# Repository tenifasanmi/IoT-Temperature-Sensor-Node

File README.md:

# IoT Temperature Sensor Node
## Overview
This project demonstrates fog and cloud computing for IoT sensor data, differing in terms of latency and response time.
A DHT11 sensor connected to an ESP32 collects temperature and humidity data, and sends it to a Raspberry Pi acting as a fog node (local processing) or to a cloud server (Adafruit IO) for remote processing. For this project, I made use of Freenove's ESP32 WROOM Development Board. This choice was mainly due to its small size and wifi/Bluetooth capabilities. I couldn't find a footprint/symbol for this board online for use in my schematics, so I designed the PCB using a pin header connector to connect my board to the PCB. The pin headers correspond with the pins of the devboard and allow for connection between the board and the temperature sensor. The DHT11 can also be interchanged with the DHT22 temperature sensor, which offers higher accuracy and a wider temperature range, but is more costly.
Initially, this system was tested using a Raspberry Pi 4B as the sensor node and my local PC as the fog node for processing. Due to constraints in real-world applications, such as size, as well as the fact that this is a small-scale device which doesn't require all the functionalities of a Raspberry Pi 4B, this project was switched to an ESP32. For this project, the code was written in Python using the Raspberry Pi; however, I have decided to implement it in C for the ESP32. The functionality remains the same for both implementations.

## Raspberry Pi-based IoT Sensor Node
### Workflow
* The Raspberry Pi reads data from the DHT11 sensor.
* It publishes the readings to the PC (Fog Node) via MQTT.
* The Fog Node locally processes the data, sends a feedback message (e.g., “Too cold, turn on heater”), and forwards the data to the cloud.
* The Cloud (Adafruit IO) stores the readings, allows remote access, and sends cloud-level feedback back to the system.

### Materials Used
* Raspberry Pi 4B
* DHT11 Sensor
* Fog Node (Windows PC)
* Cloud Server (Adafruit IO)
* MQTT Broker

#### Wiring Diagram
<p align=center>

#### Schematic
<p align=center>

## ESP 32-based IoT Sensor Node
### Workflow
* The ESP32 reads data from the DHT11 sensor.
* It publishes the readings to the Raspberry Pi (Fog Node) via MQTT.
* The Fog Node locally processes the data, sends a feedback message (e.g., “Too cold, turn on heater”), and forwards the data back to the ESP32.
* For the Cloud implementation using Adafruit IO, the data is sent to the cloud server, where data processing takes place feedback.

### Materials Used
* ESP32-WROOM-32E Dev Board
* DHT11 Sensor
* Fog Node (Raspberry Pi)
* Custom PCB for connecting DHT11 to ESP32-WROOM-32E Dev Board
* MQTT Broker

#### Custom PCB Connection Board
<p align=center /p>

#### Schematic
<p align = center /p>

## Results
Fog processing provides quicker response times since computations occur closer to the sensor, while cloud processing offers better scalability and data visibility at the cost of higher latency.

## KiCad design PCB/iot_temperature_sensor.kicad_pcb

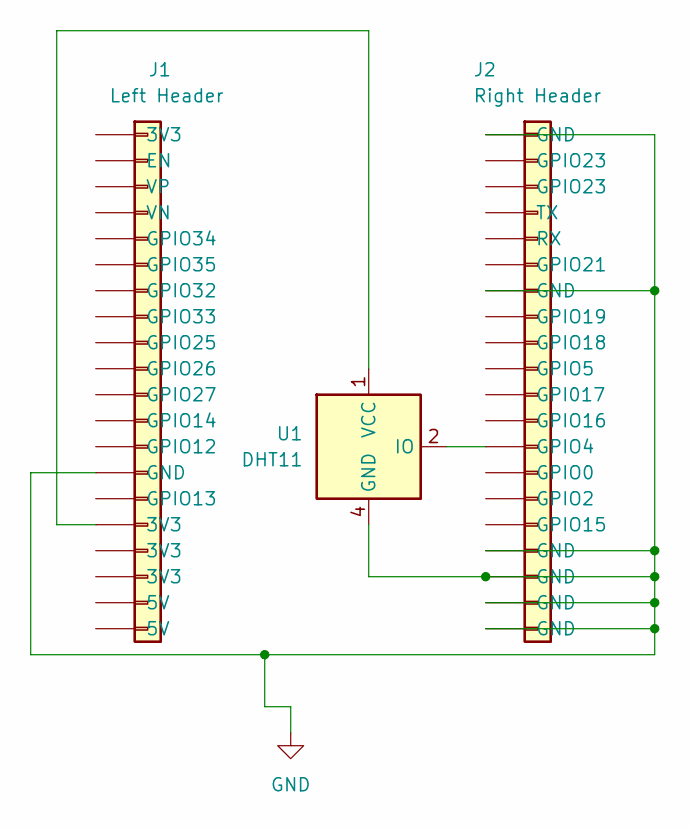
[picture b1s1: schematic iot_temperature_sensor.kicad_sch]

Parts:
J1: Left Header; PinHeader_1x20_P2.54mm_Vertical
J2: Right Header; PinHeader_1x20_P2.54mm_Vertical
U1: DHT11; Aosong_DHT11_5.5x12.0_P2.54mm

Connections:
GND: J1.14 (GND), J2.1 (GND), J2.7 (GND), J2.17 (GND), J2.18 (GND), J2.19 (GND), J2.20 (GND), U1.4 (GND)
unnamed: J2.13 (GPIO4), U1.2 (IO)
unnamed: J1.16 (3V3), U1.1 (VCC)

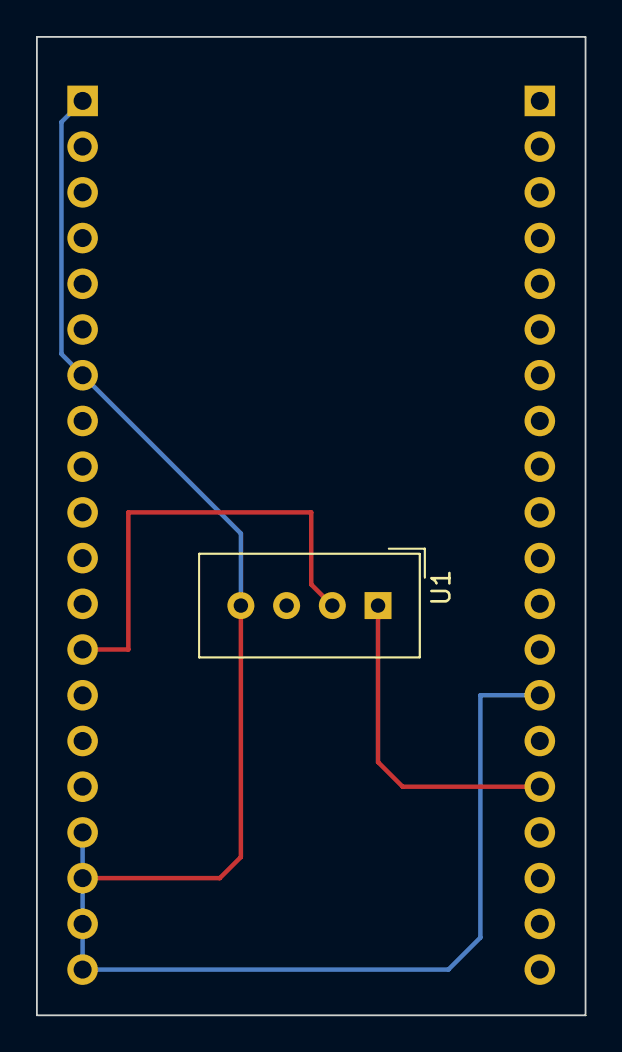
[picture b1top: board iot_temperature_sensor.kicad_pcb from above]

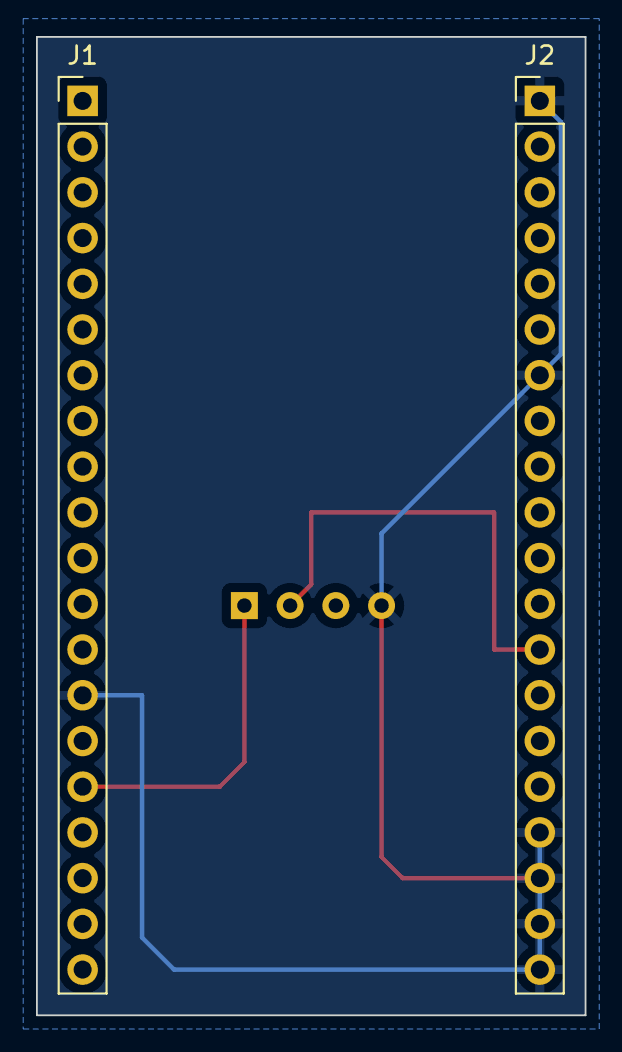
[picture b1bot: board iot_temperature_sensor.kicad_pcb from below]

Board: 2 copper layers, 30.5 x 54.4 mm, 3 parts (2 on the bottom side), 3 nets.

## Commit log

2025-10-21 Rename for_processing_sensor.py to fog_processing_sensor.py
2025-10-25 Create Pcb
2025-10-25 Rename Screenshot 2025-10-25 022249.png to PCB 3D view with component.png
2025-10-27 Rename fog_node.py to local_fog_node.py
2025-10-27 Rename Screenshot 2025-10-26 232426.png to Fog computing Results.png
2025-10-27 Rename Screenshot 2025-10-26 232757.png to Adafruit IO live feed data.png
2025-10-27 Rename Screenshot 2025-10-26 232807.png to Adafruit IO Actions.png
2025-10-27 Rename Screenshot 2025-10-26 232816.png to Results Displayed on Raspberry Pi.png
